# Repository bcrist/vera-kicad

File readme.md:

This repo contains KiCAD design files for my hobby discrete-logic CPU, Vera.

You can find the main repo here: https://github.com/bcrist/vera

This repo is kept separately because KiCAD files tend to get very large, and I want to be able to ensure that the main repo doesn't get bloated with them.  The main repo instead has this repo as a shallow submodule.  Yes, I could have just used LFS instead, but I'd rather it be completely separate.

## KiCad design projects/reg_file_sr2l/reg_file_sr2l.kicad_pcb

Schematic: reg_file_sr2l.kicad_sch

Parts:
C1, C6: 10u; C_0805
C2, C5, C7, C10, C13, C14, C15, C16, C17, C18, C19, C20, C21, C22, C23, C24, C25, C26, C27, C28, C29, C30, C31, C32, C33, C34, C35, C36, C37, C38, C39, C40: 100n; C_0402
C3, C4, C8, C9: 22u; C_0805
C11, C12: 1u; C_0402
J1, J2, J3: 2M11_2M71; CardEdge_PCIe_x16
L1, L2: 3.3u; L_taiyo_yuden_nrs5040
Q1, Q2: 2N3904; U_TO92-3
R1: 33k2 1%; R_0402
R2, R6: 10k 1%; R_0402
R3, R7: LIST; R_0402
R4, R8: 15m; R_1206
R5: 56k2 1%; R_0402
R9, R10, R11, R12: 1k; R_0402
U1, U3: AP62300TWU-7; U_SOT23-6
U2, U4: EMC1702; U_QFN-12_4x4_P0.8_EP2.1x2.1
U5: MIC5504-1.8YM5; U_SOT23-5
U6, U7: CY7C0241-15AC; U_QFP-100_14x14_P0.5
U8, U9, U10, U11: LC4032x-T48; U_QFP-48_7x7_P0.5
U12: TXU0304
U13: 74x2G34; U_SOT363_1.25x2.1_P0.65
U14, U15: 74x541; U_TSSOP-20_4.4x6.5_P0.65
U16: 74x138; U_TSSOP-16_4.4x5_P0.65
U17: 74x157; U_TSSOP-16_4.4x5_P0.65
U18, U19: 74x574; U_TSSOP-20_4.4x6.5_P0.65

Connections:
+1V8: C17.1, C18.1, C19.1, C20.1, C26.1, C27.1, C28.1, C29.1, C33.1, U8.12 (VCC_{CORE}), U8.36 (VCC_{CORE}), U9.12 (VCC_{CORE}), U9.36 (VCC_{CORE}), U10.12 (VCC_{CORE}), U10.36 (VCC_{CORE}), U11.12 (VCC_{CORE}), U11.36 (VCC_{CORE}), U12.14 (VCC_{B})
+5V: C13.1, C14.1, C23.1, R8.1, U4.11 (SENSE-), U6.12 (+5V), U6.17 (+5V), U6.36 (~ROE), U6.39 (~RSEM), U6.62 (M~S), U6.86 (~LSEM), U6.87 (~LWE), U6.88 (+5V), U7.12 (+5V), U7.17 (+5V), U7.36 (~ROE), U7.39 (~RSEM), U7.62 (M~S), U7.86 (~LSEM), U7.87 (~LWE), U7.88 (+5V)
+12V: C1.1, C6.1, J1.A1, J1.A2, J1.A3, J1.B1, J1.B2, J1.B3, U1.3 (VIN), U3.3 (VIN)
/3v3: C3.1, C4.1, C5.1, L1.1, R1.1, R4.2, U2.1 (VDD), U2.12 (SENSE+)
/5v0: C8.1, C9.1, C10.1, L2.1, R5.1, R8.2, U4.1 (VDD), U4.12 (SENSE+)
/C_ASN4_{0}: U18.15 (Q4), U19.2 (D0)
/C_ASN4_{1}: U18.14 (Q5), U19.3 (D1)
/C_ASN4_{2}: U18.13 (Q6), U19.4 (D2)
/C_ASN4_{3}: U18.12 (Q7), U19.5 (D3)
/N_ASN4_{0}: U17.4, U18.2 (D0)
/N_ASN4_{1}: U17.7, U18.3 (D1)
/N_ASN4_{2}: U17.9, U18.4 (D2)
/N_ASN4_{3}: U17.12, U18.5 (D3)
/RCLK: J1.A49, U8.19 (CLK2), U9.42 (CLK3), U10.43 (CLK0), U11.43 (CLK0), U18.11, U19.11
/SCL: J1.B5, U2.8 (SCL), U4.8 (SCL)
/SDA: J1.B6, U2.7 (SDA), U4.7 (SDA)
/SLEEPING: J1.A47, U6.40 (~RCE), U6.85 (~LCE), U7.40 (~RCE), U7.85 (~LCE)
/SW3v3: C2.2, L1.2, U1.2 (SW)
/SW5v0: C7.2, L2.2, U3.2 (SW)
/S_ASN4_{0}: J2.A1, U18.6 (D4), U18.19 (Q0)
/S_ASN4_{1}: J2.A2, U18.7 (D5), U18.18 (Q1)
/S_ASN4_{2}: J2.A3, U18.8 (D6), U18.17 (Q2)
/S_ASN4_{3}: J2.A4, U18.9 (D7), U18.16 (Q3)
/S_BASE_RI_{0}: J1.A38, U7.66 (LA0)
/S_BASE_RI_{1}: J1.A39, U7.67 (LA1)
/S_BASE_RI_{2}: J1.A40, U7.68 (LA2)
/S_BASE_RI_{3}: J1.A41, U7.89 (~LOE)
/S_BASE_{0}: J2.A51, U7.90 (LD0)
/S_BASE_{1}: J2.A52, U7.91 (LD1)
/S_BASE_{2}: J2.A53, U7.93 (LD2)
/S_BASE_{3}: J2.A54, U7.94 (LD3)
/S_BASE_{4}: J2.A55, U7.95 (LD4)
/S_BASE_{5}: J2.A56, U7.96 (LD5)
/S_BASE_{6}: J2.A57, U7.97 (LD6)
/S_BASE_{7}: J2.A58, U7.98 (LD7)
/S_BASE_{8}: J2.A59, U7.3 (LD8)
/S_BASE_{9}: J2.A60, U7.4 (LD17)
/S_BASE_{10}: J2.A61, U7.5 (LD11)
/S_BASE_{11}: J2.A62, U7.6 (LD12)
/S_BASE_{12}: J2.A63, U7.7 (LD13)
/S_BASE_{13}: J2.A64, U7.8 (LD14)
/S_BASE_{14}: J2.A65, U7.10 (LD15)
/S_BASE_{15}: J2.A66, U7.11 (LD16)
/S_JH_SRC_{0}: J1.A27, U9.17 (A15)
/S_JH_SRC_{1}: J1.A28, U9.18 (CLK1)
/S_JH_SRC_{2}: J1.A29, U9.19 (CLK2)
/S_JL_SRC_{0}: J1.A30, U8.10 (A11), U9.9 (A10)
/S_JL_SRC_{1}: J1.A31, U8.14 (A12), U9.10 (A11)
/S_J_{0}: J3.A28, U8.20 (B0)
/S_J_{1}: J3.A29, U8.21 (B1)
/S_J_{2}: J3.A30, U8.22 (B2)
/S_J_{3}: J3.A31, U8.23 (B3)
/S_J_{4}: J3.A32, U8.24 (B4)
/S_J_{5}: J3.A33, U8.26 (B5)
/S_J_{6}: J3.A34, U8.27 (B6)
/S_J_{7}: J3.A35, U8.28 (B7)
/S_J_{8}: J3.A36, U9.20 (B0)
/S_J_{9}: J3.A37, U9.21 (B1)
/S_J_{10}: J3.A38, U9.22 (B2)
/S_J_{11}: J3.A39, U9.23 (B3)
/S_J_{12}: J3.A40, U9.24 (B4)
/S_J_{13}: J3.A41, U9.26 (B5)
/S_J_{14}: J3.A42, U9.27 (B6)
/S_J_{15}: J3.A43, U9.28 (B7)
/S_J_{16}: J3.A44, U14.18 (Y0)
/S_J_{17}: J3.A45, U14.17 (Y1)
/S_J_{18}: J3.A46, U14.16 (Y2)
/S_J_{19}: J3.A47, U14.15 (Y3)
/S_J_{20}: J3.A48, U14.14 (Y4)
/S_J_{21}: J3.A49, U14.13 (Y5)
/S_J_{22}: J3.A50, U14.12 (Y6)
/S_J_{23}: J3.A51, U14.11 (Y7)
/S_J_{24}: J3.A52, U15.18 (Y0)
/S_J_{25}: J3.A53, U15.17 (Y1)
/S_J_{26}: J3.A54, U15.16 (Y2)
/S_J_{27}: J3.A55, U15.15 (Y3)
/S_J_{28}: J3.A56, U15.14 (Y4)
/S_J_{29}: J3.A57, U15.13 (Y5)
/S_J_{30}: J3.A58, U15.12 (Y6)
/S_J_{31}: J3.A59, U15.11 (Y7)
/S_K_SRC_{0}: J1.A32, U8.15 (A13), U9.14 (A12)
/S_K_SRC_{1}: J1.A33, U8.16 (A14), U9.15 (A13)
/S_K_SRC_{2}: J1.A34, U8.17 (A15), U9.16 (A14)
/S_K_{0}: J3.A12, U8.31 (B8)
/S_K_{1}: J3.A13, U8.32 (B9)
/S_K_{2}: J3.A14, U8.33 (B10)
/S_K_{3}: J3.A15, U8.34 (B11)
/S_K_{4}: J3.A16, U8.38 (B12)
/S_K_{5}: J3.A17, U8.39 (B13)
/S_K_{6}: J3.A18, U8.40 (B14)
/S_K_{7}: J3.A19, U8.41 (B15_{GOE})
/S_K_{8}: J3.A20, U9.31 (B8)
/S_K_{9}: J3.A21, U9.32 (B9)
/S_K_{10}: J3.A22, U9.33 (B10)
/S_K_{11}: J3.A23, U9.34 (B11)
/S_K_{12}: J3.A24, U9.38 (B12)
/S_K_{13}: J3.A25, U9.39 (B13)
/S_K_{14}: J3.A26, U9.40 (B14)
/S_K_{15}: J3.A27, U9.41 (B15_{GOE})
/S_RSN_{0}: J2.A49, U6.69 (LA3), U7.69 (LA3)
/S_RSN_{1}: J2.A48, U6.70 (LA4), U7.70 (LA4)
/S_RSN_{2}: J2.A47, U6.71 (LA5), U7.71 (LA5)
/S_RSN_{3}: J2.A46, U6.76 (LA6), U7.76 (LA6)
/S_RSN_{4}: J2.A45, U6.77 (LA7), U7.77 (LA7)
/S_RSN_{5}: J2.A44, U6.78 (LA8), U7.78 (LA8)
/S_SR2_RI_{0}: J1.A35, U6.66 (LA0)
/S_SR2_RI_{1}: J1.A36, U6.67 (LA1)
/S_SR2_RI_{2}: J1.A37, U6.68 (LA2)
/S_SR2_{0}: U6.90 (LD0), U8.45 (A1), U10.44 (A0_{GOE})
/S_SR2_{1}: U6.91 (LD1), U8.46 (A2), U10.45 (A1)
/S_SR2_{2}: U6.93 (LD2), U8.47 (A3), U10.46 (A2)
/S_SR2_{3}: U6.94 (LD3), U8.48 (A4), U10.47 (A3)
/S_SR2_{4}: U6.95 (LD4), U8.2 (A5), U10.48 (A4)
/S_SR2_{5}: U6.96 (LD5), U8.3 (A6), U10.2 (A5)
/S_SR2_{6}: U6.97 (LD6), U8.4 (A7), U10.3 (A6)
/S_SR2_{7}: U6.98 (LD7), U8.7 (A8), U10.4 (A7)
/S_SR2_{8}: U6.3 (LD8), U9.44 (A0_{GOE}), U11.44 (A0_{GOE})
/S_SR2_{9}: U6.4 (LD17), U9.45 (A1), U11.45 (A1)
/S_SR2_{10}: U6.5 (LD11), U9.46 (A2), U11.46 (A2)
/S_SR2_{11}: U6.6 (LD12), U9.47 (A3), U11.47 (A3)
/S_SR2_{12}: U6.7 (LD13), U9.48 (A4), U11.48 (A4)
/S_SR2_{13}: U6.8 (LD14), U9.2 (A5), U11.2 (A5)
/S_SR2_{14}: U6.10 (LD15), U9.3 (A6), U11.3 (A6)
/S_SR2_{15}: U6.11 (LD16), U9.4 (A7), U11.4 (A7), U13.1, U13.3
/S_~JL_SX: U9.8 (A9), U14.19 (~OE), U15.19 (~OE)
/TCK: U8.11 (TCK), U9.11 (TCK), U10.11 (TCK), U11.11 (TCK), U12.13 (B1_{Y})
/TMS: U8.25 (TMS), U9.25 (TMS), U10.25 (TMS), U11.25 (TMS), U12.12 (B2_{Y})
/T_ASN4_{0}: U17.3, U19.19 (Q0)
/T_ASN4_{1}: U17.6, U19.18 (Q1)
/T_ASN4_{2}: U17.10, U19.17 (Q2)
/T_ASN4_{3}: U17.13, U19.16 (Q3)
/T_L_{0}: J1.A51, U10.20 (B0)
/T_L_{1}: J1.A52, U10.21 (B1)
/T_L_{2}: J1.A53, U10.22 (B2)
/T_L_{3}: J1.A54, U10.23 (B3)
/T_L_{4}: J1.A55, U10.24 (B4)
/T_L_{5}: J1.A56, U10.26 (B5)
/T_L_{6}: J1.A57, U10.27 (B6)
/T_L_{7}: J1.A58, U10.28 (B7)
/T_L_{8}: J1.A59, U11.20 (B0)
/T_L_{9}: J1.A60, U11.21 (B1)
/T_L_{10}: J1.A61, U11.22 (B2)
/T_L_{11}: J1.A62, U11.23 (B3)
/T_L_{12}: J1.A63, U11.24 (B4)
/T_L_{13}: J1.A64, U11.26 (B5)
/T_L_{14}: J1.A65, U11.27 (B6)
/T_L_{15}: J1.A66, U11.28 (B7)
/T_PN_{0}: J2.A5, U10.31 (B8)
/T_PN_{1}: J2.A6, U10.32 (B9)
/T_PN_{2}: J2.A7, U10.33 (B10)
/T_PN_{3}: J2.A8, U10.34 (B11)
/T_PN_{4}: J2.A9, U10.38 (B12)
/T_PN_{5}: J2.A10, U10.39 (B13)
/T_PN_{6}: J2.A11, U10.40 (B14)
/T_PN_{7}: J2.A12, U10.41 (B15_{GOE})
/T_PN_{8}: J2.A13, U11.31 (B8)
/T_PN_{9}: J2.A14, U11.32 (B9)
/T_PN_{10}: J2.A15, U11.33 (B10)
/T_PN_{11}: J2.A16, U11.34 (B11)
/T_PN_{12}: J2.A17, U11.38 (B12)
/T_PN_{13}: J2.A18, U11.39 (B13)
/T_PN_{14}: J2.A19, U11.40 (B14)
/T_PN_{15}: J2.A20, U11.41 (B15_{GOE})
/T_RSN_{0}: J2.A42, U6.56 (RA3), U7.56 (RA3)
/T_RSN_{1}: J2.A41, U6.55 (RA4), U7.55 (RA4)
/T_RSN_{2}: J2.A40, U6.50 (RA5), U7.50 (RA5)
/T_RSN_{3}: J2.A39, U6.49 (RA6), U7.49 (RA6)
/T_RSN_{4}: J2.A38, U6.48 (RA7), U7.48 (RA7)
/T_RSN_{5}: J2.A37, U6.47 (RA8), U7.47 (RA8)
/T_SR2_WI_{0}: J1.A42, U6.59 (RA0), U7.59 (RA0), U16.1
/T_SR2_WI_{1}: J1.A43, U6.58 (RA1), U7.58 (RA1), U16.2
/T_SR2_WI_{2}: J1.A44, U6.57 (RA2), U7.57 (RA2), U16.3
/T_SR2_WSRC_{0}: J1.A45, U8.18 (CLK1), U10.19 (CLK2), U11.19 (CLK2)
/T_SR2_WSRC_{1}: J1.A46, U8.9 (A10), U10.42 (CLK3), U11.42 (CLK3)
/T_SR2_{0}: U6.14 (RD0), U7.14 (RD0), U10.7 (A8), U17.2
/T_SR2_{1}: U6.15 (RD1), U7.15 (RD1), U10.8 (A9), U17.5
/T_SR2_{2}: U6.16 (RD2), U7.16 (RD2), U10.9 (A10), U17.11
/T_SR2_{3}: U6.18 (RD3), U7.18 (RD3), U10.10 (A11), U17.14
/T_SR2_{4}: U6.19 (RD4), U7.19 (RD4), U10.14 (A12)
/T_SR2_{5}: U6.20 (RD5), U7.20 (RD5), U10.15 (A13)
/T_SR2_{6}: U6.21 (RD6), U7.21 (RD6), U10.16 (A14)
/T_SR2_{7}: U6.26 (RD7), U7.26 (RD7), U10.17 (A15)
/T_SR2_{8}: U6.22 (RD8), U7.22 (RD8), U11.7 (A8)
/T_SR2_{9}: U6.23 (RD17), U7.23 (RD17), U11.8 (A9)
/T_SR2_{10}: U6.29 (RD11), U7.29 (RD11), U11.9 (A10)
/T_SR2_{11}: U6.30 (RD12), U7.30 (RD12), U11.10 (A11)
/T_SR2_{12}: U6.31 (RD13), U7.31 (RD13), U11.14 (A12)
/T_SR2_{13}: U6.32 (RD14), U7.32 (RD14), U11.15 (A13)
/T_SR2_{14}: U6.33 (RD15), U7.33 (RD15), U11.16 (A14)
/T_SR2_{15}: U6.35 (RD16), U7.35 (RD16), U11.17 (A15)
/T_~INHIBIT_W: J1.A48, U8.42 (CLK3)
/T_~SR2_WE_NOCLK: U8.8 (A9), U16.5
/T_~SR2_WE: U6.37 (~RWE), U7.37 (~RWE), U8.44 (A0_{GOE})
/WCLK: J1.A50, U8.43 (CLK0)
/~RESET: J1.A8
/~RESETod: J1.A7
GND: C1.2, C3.2, C4.2, C5.2, C6.2, C8.2, C9.2, C10.2, C11.2, C12.2, C13.2, C14.2, C15.2, C16.2, C17.2, C18.2, C19.2, C20.2, C21.2, C22.2, C23.2, C24.2, C25.2, C26.2, C27.2, C28.2, C29.2, C30.2, C31.2, C32.2, C33.2, C34.2, C35.2, C36.2, C37.2, C38.2, C39.2, C40.2, J1.A4, J1.A5, J1.A6, J1.B4, J1.B7, J1.B51, J1.B52, J1.B53, J1.B54, J1.B55, J1.B56, J1.B57, J1.B58, J1.B59, J1.B60, J1.B61, J1.B62, J1.B63, J1.B64, J1.B65, J1.B66, R2.2, R3.2, R6.2, R7.2, R9.2, R10.2, R11.2, R12.2, U1.1 (GND), U2.EP (GND), U3.1 (GND), U4.EP (GND), U5.2 (GND), U6.9 (GND), U6.13 (GND), U6.27 (RD9), U6.28 (RD10), U6.34 (GND), U6.38 (GND), U6.41 (~RHE), U6.42 (~RLE), U6.44 (RA11), U6.45 (RA10), U6.46 (RA9), U6.63 (GND), U6.79 (LA9), U6.80 (LA10), U6.81 (LA11), U6.83 (~LLE), U6.84 (~LHE), U6.89 (~LOE), U6.92 (GND), U7.9 (GND), U7.13 (GND), U7.27 (RD9), U7.28 (RD10), U7.34 (GND), U7.38 (GND), U7.41 (~RHE), U7.42 (~RLE), U7.44 (RA11), U7.45 (RA10), U7.46 (RA9), U7.63 (GND), U7.79 (LA9), U7.80 (LA10), U7.81 (LA11), U7.83 (~LLE), U7.84 (~LHE), U7.92 (GND), U8.5 (GND), U8.13 (GND), U8.29 (GND), U8.37 (GND), U9.5 (GND), U9.13 (GND), U9.29 (GND), U9.37 (GND), U10.5 (GND), U10.13 (GND), U10.29 (GND), U10.37 (GND), U11.5 (GND), U11.13 (GND), U11.29 (GND), U11.37 (GND), U13.2 (GND), U14.1 (~OE), U14.10 (GND), U15.1 (~OE), U15.10 (GND), U16.4, U16.8 (GND), U17.8 (GND), U17.15 (~E), U18.1 (~OE), U18.10 (GND), U19.1 (~OE), U19.6 (D4), U19.7 (D5), U19.8 (D6), U19.9 (D7), U19.10 (GND)
unnamed: C2.1, U1.6 (BST)
unnamed: C7.1, U3.6 (BST)
unnamed: C12.1, U5.5 (OUT)
unnamed: Q1.1 (E), U2.3 (DN)
unnamed: Q1.2 (B), Q1.3 (C), U2.2 (DP)
unnamed: Q2.1 (E), U4.3 (DN)
unnamed: Q2.2 (B), Q2.3 (C), U4.2 (DP)
unnamed: R1.2, R2.1, U1.4 (FB)
unnamed: R3.1, U2.4 (ADDR)
unnamed: R5.2, R6.1, U3.4 (FB)
unnamed: R7.1, U4.4 (ADDR)
unnamed: R9.1, U6.100 (LD9)
unnamed: R10.1, U6.99 (LD10)
unnamed: R11.1, U7.100 (LD9)
unnamed: R12.1, U7.99 (LD10)
unnamed: U13.4, U15.2 (A0), U15.3 (A1), U15.4 (A2), U15.5 (A3), U15.6 (A4), U15.7 (A5), U15.8 (A6), U15.9 (A7)
unnamed: U13.6, U14.2 (A0), U14.3 (A1), U14.4 (A2), U14.5 (A3), U14.6 (A4), U14.7 (A5), U14.8 (A6), U14.9 (A7)
unnamed: U16.13, U17.1
VCC: C11.1, C15.1, C16.1, C21.1, C22.1, C24.1, C25.1, C30.1, C31.1, C32.1, C34.1, C35.1, C36.1, C37.1, C38.1, C39.1, C40.1, R4.1, U2.11 (SENSE-), U5.1 (IN), U5.3 (EN), U8.6 (VCCO_{0}), U8.30 (VCCO_{1}), U9.6 (VCCO_{0}), U9.30 (VCCO_{1}), U10.6 (VCCO_{0}), U10.30 (VCCO_{1}), U11.6 (VCCO_{0}), U11.30 (VCCO_{1}), U12.1 (VCC_{A}), U12.8 (OE), U13.5 (VCC), U14.20 (VCC), U15.20 (VCC), U16.6, U16.16 (VCC), U17.16 (VCC), U18.20 (VCC), U19.20 (VCC)

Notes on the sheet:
Taiyo Yuden NRS5040T3R3NMGJ
LIST (5%) 0 100 180 300 430 560 750 1k27 1k6 2k 2k7 3k6 5k6 open
Susumu KRL1632E-M-R015-F-T5
TL = TQ
Address 0x4C 0x4D 0x4E 0x4F 0x48 0x49 0x4A 0x4B 0x28 0x29 0x2A 0x2B 0x2C 0x18

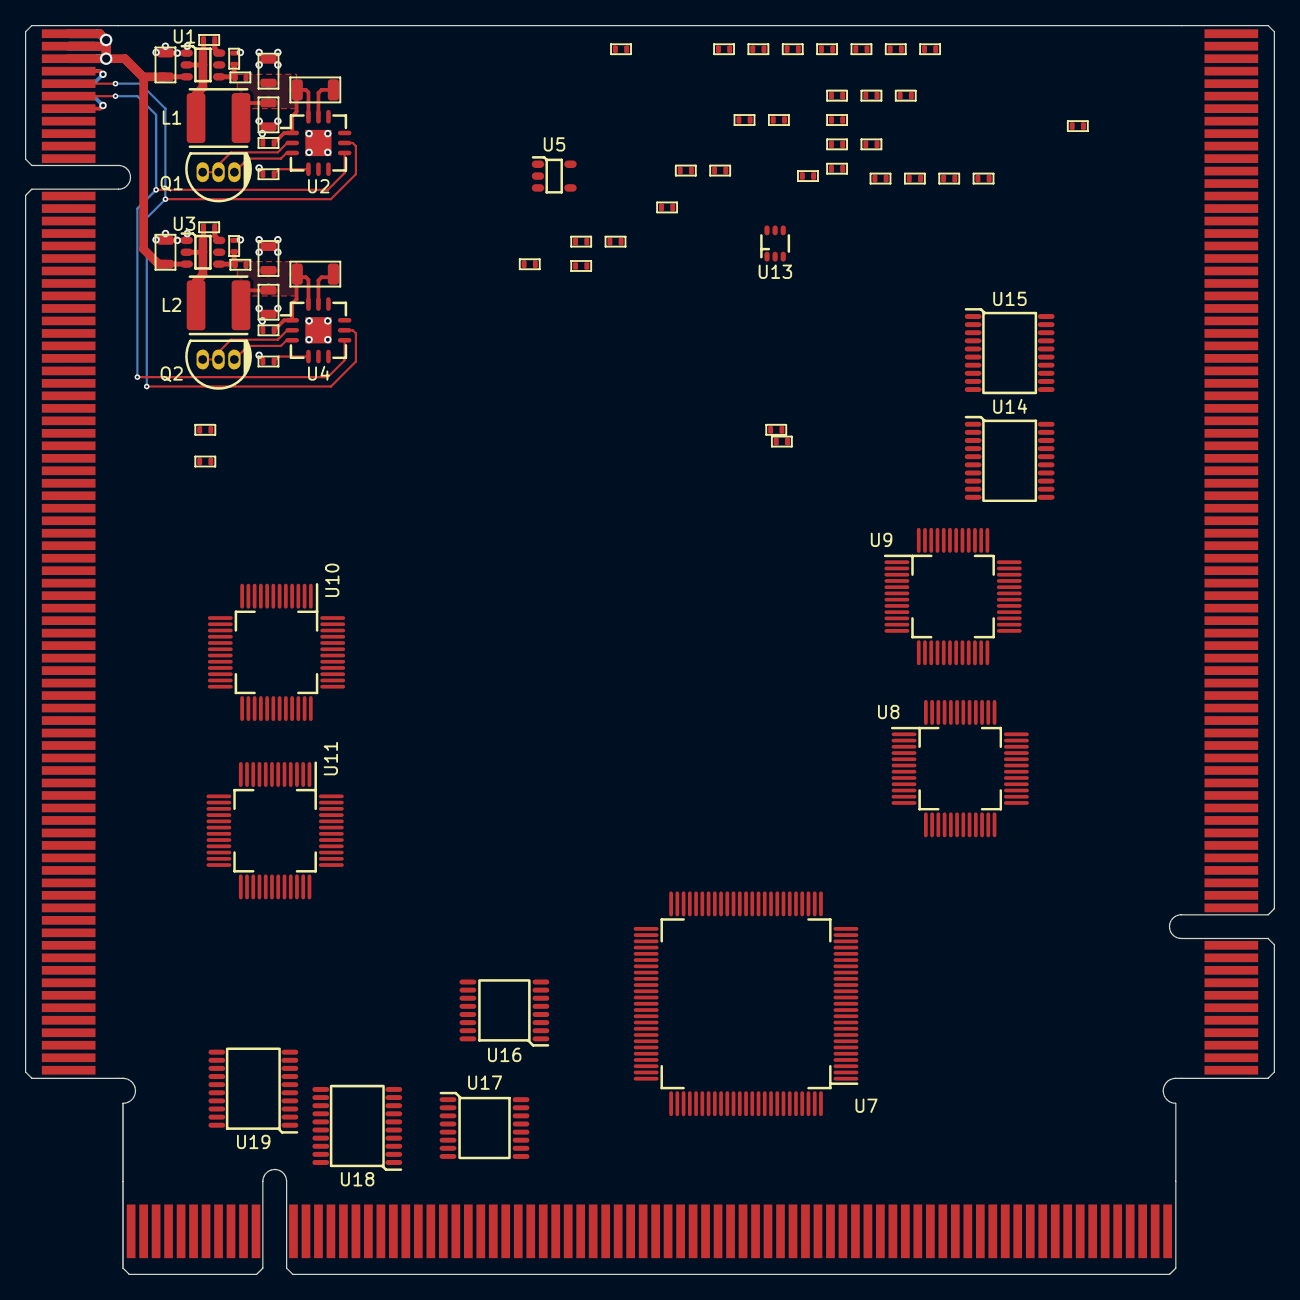
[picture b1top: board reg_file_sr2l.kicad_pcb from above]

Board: 4 copper layers, 100.0 x 100.0 mm, 77 parts (1 on the bottom side), 214 nets.

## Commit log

2023-03-17 sr2 work
2023-06-03 update readme for repo renaming
